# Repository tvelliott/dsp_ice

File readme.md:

<html>

<BR>
<BR><B>DSP_ICE</B>
<BR>
<B>Project Description</B>
<p>DSP_ICE is an ICE40-8K FPGA dev system that has been developed using gcc and
Project Icestorm toolchains.  The hardware has been fully tested except for the
PDM microphone.  Firmware/HDL examples are provided to test the hardware,
including an 8-channel, multi-waveform audio synthesizer and peak amplitude,
frequency measurement via CMSIS DSP FFT functions utilizing the LTC1420 ADC
expansion module.
</p>
<BR>
<B>Why Develop Another ICE40 Dev Board?</B>
<p>
DSP ICE was developed because other boards didn't have all the features desired.
The ultimate goal is to develop an SDR with swappable analog/RF front-ends.
Desired features that drove the development were:
<BR>1) 10/100 Ethernet
<BR>2) 8K ICE 40 device that could be done with 5mil spaced, 4-layer pcb
<BR>3) I2S audio output
<BR>4) STM32F4 device that is foot-print compatible with F7 and H7 series for future
<BR>5) 16-bit FSMC memory-bus interface between the MCU and FPGA
<BR>6) Low-noise power supplies with plenty of current for expansion modules
<BR>7) Plenty of expansion I/O pins designed to utilize upper limits on frequency with ICE40
</p>

<H3><a href="https://raw.githubusercontent.com/tvelliott/dsp_ice/master/firmware/audio_synth_test/dsp_ice_audio_synth_test.mp3">8-channel audio synth test.mp3</a> audio output from example audio-synth implemented in Verilog</H3> 

<BR>
<BR>
<B>Features:</B>
<BR>
<BR>STM32F417 MCU  (upgradable with drop-in for F7 and H7 series up to 400 MHz)
<BR>ICE40HX8K-CT256 FPGA (largest ICE40 device available)
<BR>16-Bit FSMC interface between MCU <-> FPGA.  Interface clock is running @ 80 MHz
<BR>10-100 Mbps Ethernet interface  (firmware includes iperf3 server for testing bandwidth)
<BR>ST-Link programming header  (can use STM32F4-Discovery as a programming device)
<BR>I2S Audio interface  (firmware includes example of 8-channel audio synth with sawtooth, pulse, noise waveforms and a song playback via I2S)
<BR>4 PMOD-Like ports  (include 5V and 3.3V and 8 I/O pins x 4)
<BR>USB FTDI-based serial interface  (update 8/13/2017 firmware to test the uart interface has been added)
<BR>40 MHz TCXO crystal driving both FPGA and MCU  (MCU clock div/2)

<BR>
<BR>
<B>Verilog Source Is Here</B>
<BR>
<a href="https://github.com/tvelliott/dsp_ice/tree/master/firmware/fpga/src">/firmware/fpga/src</a>
<BR>

<BR>
<B>DSP ICE MCU 16-bit Memory-Mapped FPGA registers</B>
<BR>
<pre>
0x60000000   spi1_ctrl
0x60000002   spi1_data_in
0x60000004   spi1_data_out
0x60000006   spi1_cs_ctrl

0x60000008   spi2_ctrl
0x6000000a   spi2_data_in
0x6000000c   spi2_data_out
0x6000000e   spi2_cs_ctrl

0x60000010   adc_data  (LTC1420 hw module, read-only, bit0 is OF) 

0x60001000   audio_ctrl
0x60001002   left_sample
0x60001004   right_sample
0x60001006   tone1_freq
0x60001008   tone2_freq
0x6000100a   tone3_freq
0x6000100c   tone4_freq
0x6000100e   tone5_freq
0x60001010   tone6_freq
0x60001012   tone7_freq
0x60001014   tone8_freq
0x60001016   waveform_ctrl

0x6000f000   16-bit random number (ro)
</pre>

<B>PCB Design</B>
<BR>4 layers
<BR>Designed for OSH Park 4 layer service.  (5 mil spacing)
<BR>Have assembled 4 boards without any connectivity issues on the 256-pin BGA

<B>Left To Do</B>
<BR>The PDM michrophone has not been tested yet due to trouble getting the part.  
<BR>Digikey has the part in stock, but Cirrus Logic will not allow them to sell 
<BR>it to certain individuals including the author of this project. There were
<BR>no further explanations from Cirrus Logic.
<BR>
<BR>
<B>Building The Firmware</B>
<PRE>
Instructions (tested on Debian 8 system)

1) download GNU ARM Embedded Toolchain from here:

<a href="https://launchpad.net/gcc-arm-embedded"> https://launchpad.net/gcc-arm-embedded </a>

The test firmare was compiled with version:
gcc-arm-none-eabi-5_4-2016q3-20160926-linux.tar.bz2

2) *edit the makedefs_fp and change PRE_PREFIX to point to the absolute path of
the toolchain directory *optionally,  move the uncompressed toolchain folder to
the project folder and rename to gnu_arm_toolchain

3) From the project directory, In order to re-build the FPGA binary image, type
'sh build_fpga_image.sh'  (requires that Project Icestorm tools are installed)

  yosys  (synthesis tool)  <a href="http://www.clifford.at/icestorm/"> http://www.clifford.at/icestorm/</a>
  ice-tools  (tools for maniuplating text/binaries and programming dev boards) 
  arache-pnr  (place-and-route)  <a href="https://github.com/cseed/arachne-pnr"> https://github.com/cseed/arachne-pnr </a>

  Note:  The fpga binary configuration image will be compressed and converted
to a header file for inclusion to the MCU firmware image:  fpga_image.h The
compressed image in fpga_image.h will be included in fpga.c on the next mcu
firmware build  (step 4) The MCU uncompresses and transfers the fpga config
image during startup.

4) From the project directory, type 'make clean' followed by  'make' The
resulting binary will be copied to /tmp folder and also the build_image folder
in the current project directory Note: the prototypes in protos can be
re-generated with 'make genprotos' if cfunctions is installed.

5) An ST-Link programmer can be used to load the resulting binary
(main_image_0x8000000.bin) to address 0x8000000

   A $15 STM32F4 Discovery board with the jumpers set to "ST Link"  (pulled
off) and a straight-thru, 6-pin 0.1" pitch cable will work.

   Follow instructions for compiling OpenOCD  <a href="http://openocd.org/"> http://openocd.org/</a>

   start the debugger:  'sudo src/openocd -s tcl -f tcl/board/stm32f4discovery.cfg'

   'telnet localhost 4444'
    > reset halt
    > flash write_image erase build_image/main_image_0x8000000.bin 0x8000000

6) Test the hardware.
   telnet 192.168.1.240   (default ip address.  edit this in config.c)
   
Trying 192.168.1.240...
Connected to 192.168.1.240.
Escape character is '^]'.

Connected To STM32F417 Running @ 168 MHz
DSP_Ice 192.168.1.240:~$ help

Available commands:

testmem
testsnd
testflash1
testflash2
testadc
reset
exit

DSP_Ice 192.168.1.240:~$ testadc
<B>Example measurement of 500 KHz sine wave, 100mVpp utilize LTC1420 ADC HW module</B>
<B>This example utilizes the CMSIS DSP Co-Processor functions of the MCU for FFT calcs.</B>
<B>Using DMA to transfer ADC results from FPGA BRAM would dramatically improve sample rate</B>
peak signal 502675.781 Hz,  0.107 Volts p-p, elapsed time 3.51 ms  
<a href="https://github.com/tvelliott/dsp_ice/blob/master/hw_modules/ltc1420_adc/fft_plot_500khz_100mVpp.gif">[see fft plot 500khz, 100mV p-p]</a> 
<a href="https://github.com/tvelliott/dsp_ice/blob/master/hw_modules/ltc1420_adc/ltc1420_capture_3.5vpp_no_filter_325khz_freqdomain.gif">[see fft plot 325Khz, 3500mV p-p]</a> 
<a href="https://github.com/tvelliott/dsp_ice/blob/master/hw_modules/ltc1420_adc/ltc1420_capture_3.5vpp_no_filter_500khz_timedomain.gif">[see time-domain plot 500khz, 3500mV p-p]</a> 
 
DSP_Ice 192.168.1.240:~$ testmem   (this tests the 16-bit FSMC memmory-mapped, MCU<->FPGA interface)

x100x (FPGA D-REG), 4015677440 bytes r/w random access, current vals: f3e7,f3e7, errors: 0
0x100x (FPGA D-REG), 4015685632 bytes r/w random access, current vals: 69c4,69c4, errors: 0
0x100x (FPGA D-REG), 4015693824 bytes r/w random access, current vals: af9a,af9a, errors: 0
0x100x (FPGA D-REG), 4015702016 bytes r/w random access, current vals: bc6a,bc6a, errors: 0
0x100x (FPGA D-REG), 4015710208 bytes r/w random access, current vals: 8732,8732, errors: 0
0x100x (FPGA D-REG), 4015718400 bytes r/w random access, current vals: 06f4,06f4, errors: 0
0x100x (FPGA D-REG), 4015726592 bytes r/w random access, current vals: 32af,32af, errors: 0
.....

DSP_Ice 192.168.1.240:~$ sh test_iperf.sh

Connecting to host 192.168.1.240, port 5201
[  4] local 192.168.1.3 port 45612 connected to 192.168.1.240 port 5201
[ ID] Interval           Transfer     Bandwidth       Retr  Cwnd
[  4]   0.00-1.00   sec  8.91 MBytes  74.7 Mbits/sec    0   14.3 KBytes       
[  4]   1.00-2.00   sec  8.88 MBytes  74.5 Mbits/sec    0   14.3 KBytes       
[  4]   2.00-3.00   sec  8.86 MBytes  74.3 Mbits/sec    0   14.3 KBytes       
[  4]   3.00-4.00   sec  8.86 MBytes  74.3 Mbits/sec    0   14.3 KBytes       
[  4]   4.00-5.00   sec  8.88 MBytes  74.5 Mbits/sec    0   14.3 KBytes       
[  4]   5.00-6.00   sec  8.87 MBytes  74.4 Mbits/sec    0   14.3 KBytes       
[  4]   6.00-7.00   sec  8.86 MBytes  74.3 Mbits/sec    0   14.3 KBytes       
[  4]   7.00-8.00   sec  8.86 MBytes  74.3 Mbits/sec    0   14.3 KBytes       
[  4]   8.00-9.00   sec  8.86 MBytes  74.3 Mbits/sec    0   14.3 KBytes       

iperf Done.

....
DSP_Ice 192.168.1.240:~$ testsnd   (song playback via 8-channel audio synth implemented on fpga)

change instrument: ch: 0,  instr: 29, mask: 5555
chan: 0, freq: 554
change instrument: ch: 1,  instr: 37, mask: 5555
chan: 1, freq: 92
change instrument: ch: 2,  instr: 16, mask: 5575
chan: 2, freq: 233
change instrument: ch: 3,  instr: 29, mask: 5575
chan: 3, freq: 370
change instrument: ch: 4,  instr: 16, mask: 5775
chan: 4, freq: 131
change instrument: ch: 5,  instr: 16, mask: 5f75
chan: 5, freq: 131
duration: 91
duration: 91
chan: 0, freq: 494
chan: 3, freq: 330
duration: 91
duration: 91
chan: 2, freq: 208
chan: 0, freq: 554
chan: 3, freq: 370
duration: 91
duration: 91
chan: 0, freq: 494
chan: 3, freq: 330
duration: 91
duration: 91
chan: 0, freq: 554
chan: 3, freq: 370
duration: 91
duration: 91

<B>Images Of LTC1420 HW Module and PCB cad rendering</B>

....
</PRE>

<B>Links To Similar Projects</B>
<BR>
<a href="https://github.com/emeb/iceRadio">https://github.com/emeb/iceRadio</a>
<BR><BR>
<B>Links To Related Resources</B>
<BR>
<BR><a href="https://launchpad.net/gcc-arm-embedded"> https://launchpad.net/gcc-arm-embedded </a>
<BR><a href="http://www.clifford.at/icestorm/"> http://www.clifford.at/icestorm/</a>
<BR><a href="https://github.com/cseed/arachne-pnr"> https://github.com/cseed/arachne-pnr </a>
<BR><a href="http://openocd.org/"> http://openocd.org/</a>

</html>

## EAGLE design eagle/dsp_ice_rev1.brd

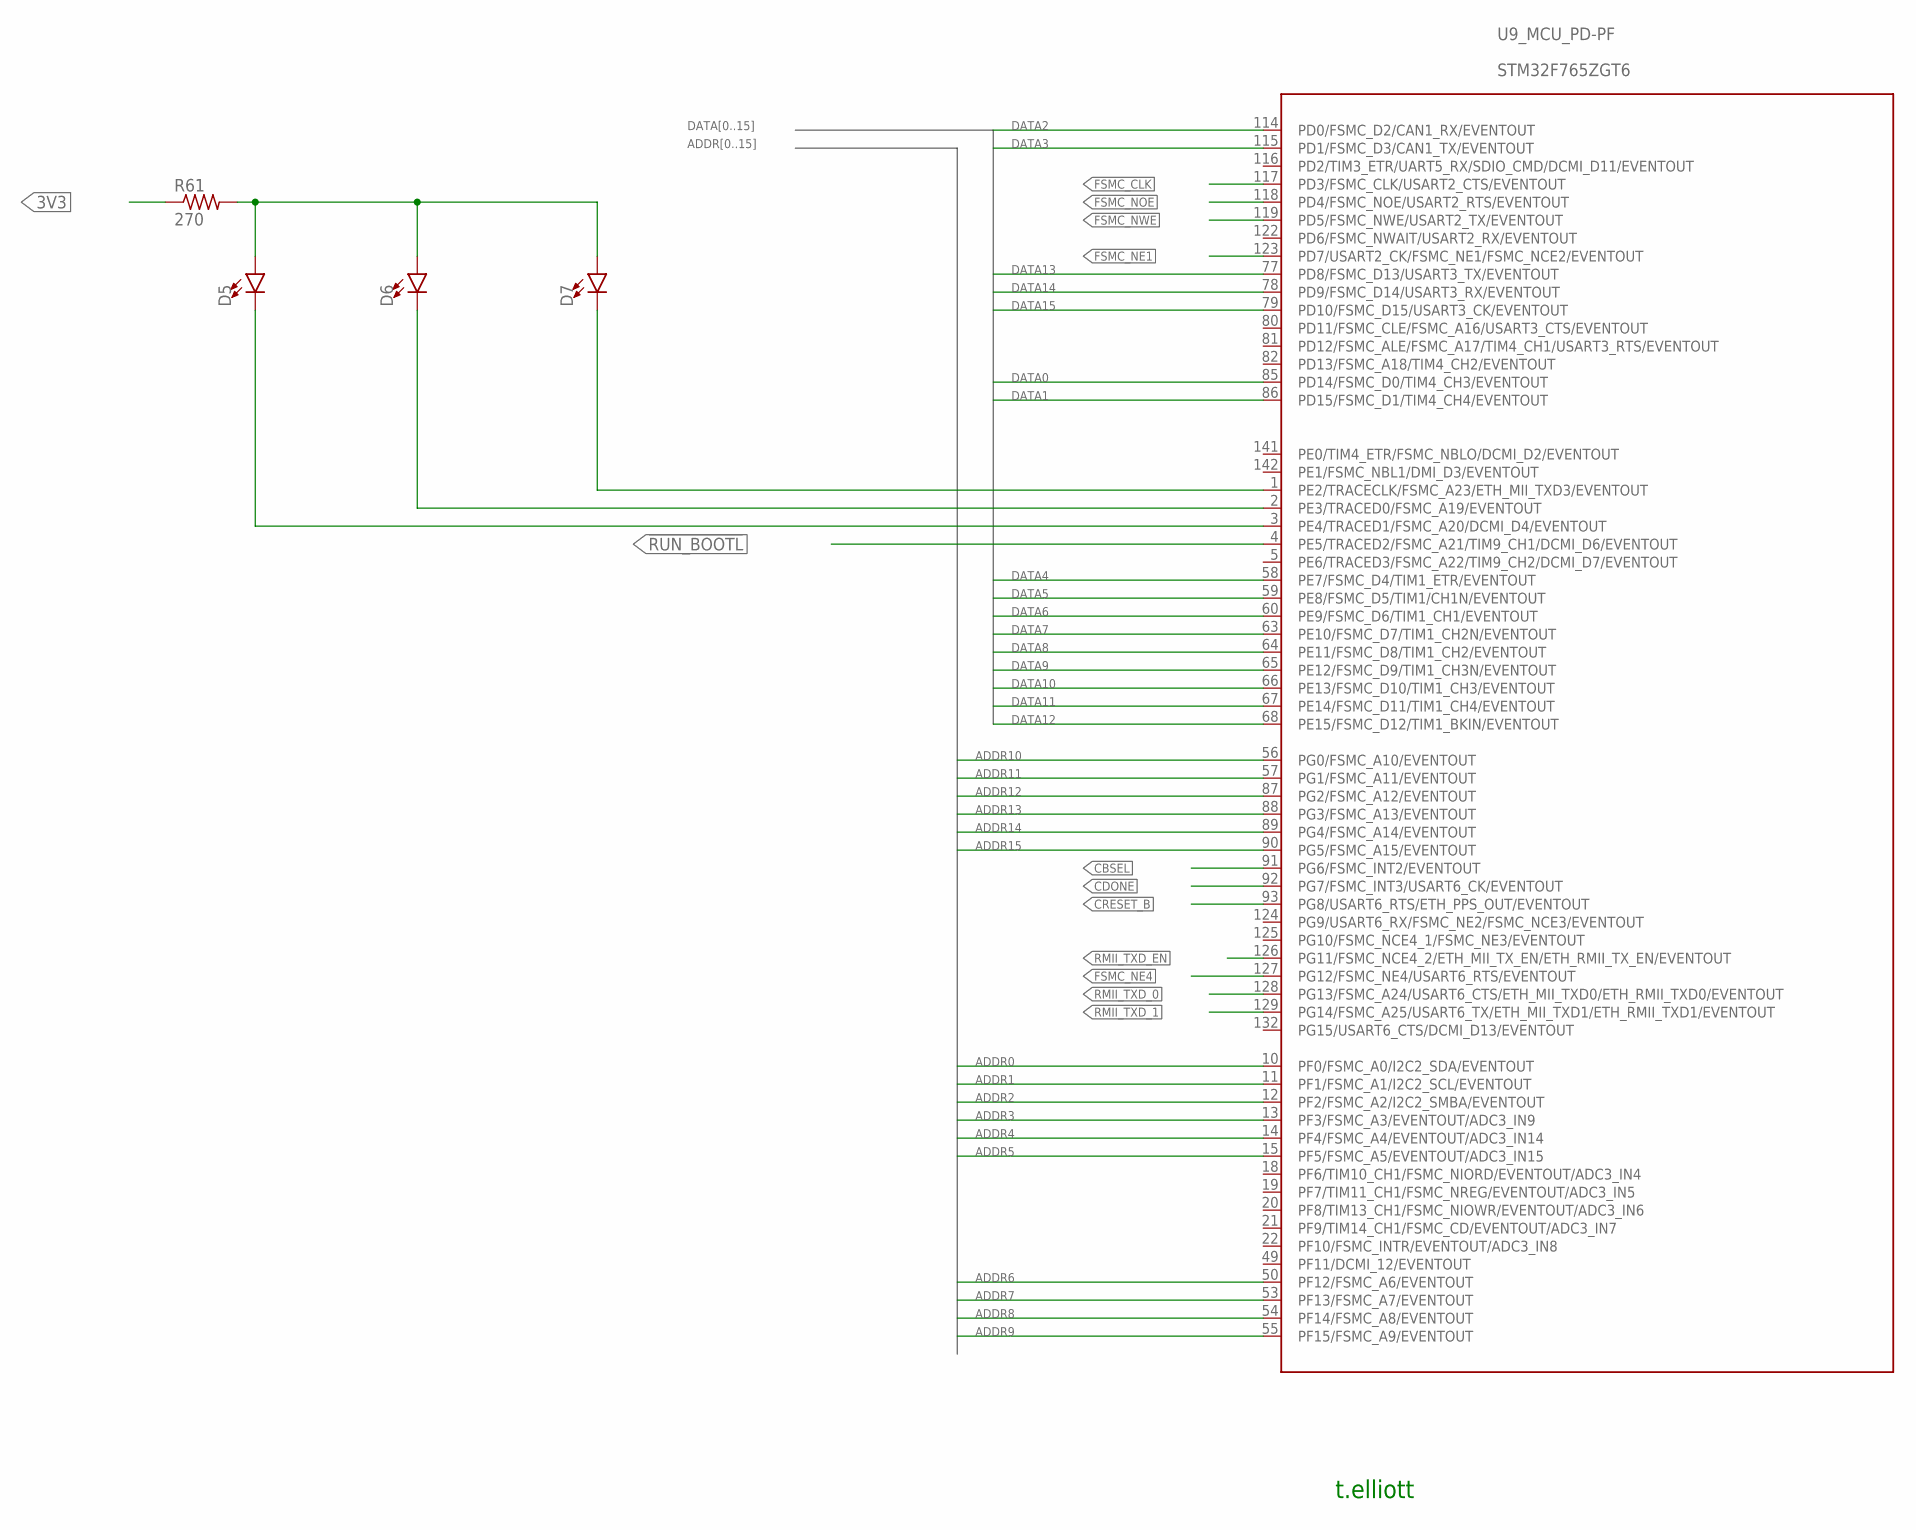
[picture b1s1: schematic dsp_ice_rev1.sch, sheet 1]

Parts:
D5, D6, D7: LED1206; LED-1206
R61: 270; R0603
U9: STM32F765ZGT6; STM32F407_144

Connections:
3V3: R61.1; also elsewhere on the board
!RUN_BOOTL: U9.4 (PE5/TRACED2/FSMC_A21/TIM9_CH1/DCMI_D6/E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); also elsewhere on the board
ADDR0: U9.10 (PF0/FSMC_A0/I2C2_SDA/EVENTOUT); also elsewhere on the board
ADDR1: U9.11 (PF1/FSMC_A1/I2C2_SCL/EVENTOUT); also elsewhere on the board
ADDR2: U9.12 (PF2/FSMC_A2/I2C2_SMBA/EVENTOUT); also elsewhere on the board
ADDR3: U9.13 (PF3/FSMC_A3/EVENTOUT/ADC3_IN9); also elsewhere on the board
ADDR4: U9.14 (PF4/FSMC_A4/EVENTOUT/ADC3_IN14); also elsewhere on the board
ADDR5: U9.15 (PF5/FSMC_A5/EVENTOUT/ADC3_IN15); also elsewhere on the board
ADDR6: U9.50 (PF12/FSMC_A6/EVENTOUT); also elsewhere on the board
ADDR7: U9.53 (PF13/FSMC_A7/EVENTOUT); also elsewhere on the board
ADDR8: U9.54 (PF14/FSMC_A8/EVENTOUT); also elsewhere on the board
ADDR9: U9.55 (PF15/FSMC_A9/EVENTOUT); also elsewhere on the board
ADDR10: U9.56 (PG0/FSMC_A10/EVENTOUT); also elsewhere on the board
ADDR11: U9.57 (PG1/FSMC_A11/EVENTOUT); also elsewhere on the board
ADDR12: U9.87 (PG2/FSMC_A12/EVENTOUT); also elsewhere on the board
ADDR13: U9.88 (PG3/FSMC_A13/EVENTOUT); also elsewhere on the board
ADDR14: U9.89 (PG4/FSMC_A14/EVENTOUT); also elsewhere on the board
ADDR15: U9.90 (PG5/FSMC_A15/EVENTOUT); also elsewhere on the board
CBSEL: U9.91 (PG6/FSMC_INT2/EVENTOUT); also elsewhere on the board
CDONE: U9.92 (PG7/FSMC_INT3/USART6_CK/EVENTOUT); also elsewhere on the board
CRESET_B: U9.93 (PG8/USART6_RTS/ETH_PPS_OUT/EVENTOUT); also elsewhere on the board
DATA0: U9.85 (PD14/FSMC_D0/TIM4_CH3/EVENTOUT); also elsewhere on the board
DATA1: U9.86 (PD15/FSMC_D1/TIM4_CH4/EVENTOUT); also elsewhere on the board
DATA2: U9.114 (PD0/FSMC_D2/CAN1_RX/EVENTOUT); also elsewhere on the board
DATA3: U9.115 (PD1/FSMC_D3/CAN1_TX/EVENTOUT); also elsewhere on the board
DATA4: U9.58 (PE7/FSMC_D4/TIM1_ETR/EVENTOUT); also elsewhere on the board
DATA5: U9.59 (PE8/FSMC_D5/TIM1/CH1N/EVENTOUT); also elsewhere on the board
DATA6: U9.60 (PE9/FSMC_D6/TIM1_CH1/EVENTOUT); also elsewhere on the board
DATA7: U9.63 (PE10/FSMC_D7/TIM1_CH2N/EVENTOUT); also elsewhere on the board
DATA8: U9.64 (PE11/FSMC_D8/TIM1_CH2/EVENTOUT); also elsewhere on the board
DATA9: U9.65 (PE12/FSMC_D9/TIM1_CH3N/EVENTOUT); also elsewhere on the board
DATA10: U9.66 (PE13/FSMC_D10/TIM1_CH3/EVENTOUT); also elsewhere on the board
DATA11: U9.67 (PE14/FSMC_D11/TIM1_CH4/EVENTOUT); also elsewhere on the board
DATA12: U9.68 (PE15/FSMC_D12/TIM1_BKIN/EVENTOUT); also elsewhere on the board
DATA13: U9.77 (PD8/FSMC_D13/USART3_TX/EVENTOUT); also elsewhere on the board
DATA14: U9.78 (PD9/FSMC_D14/USART3_RX/EVENTOUT); also elsewhere on the board
DATA15: U9.79 (PD10/FSMC_D15/USART3_CK/EVENTOUT); also elsewhere on the board
FSMC_CLK: U9.117 (PD3/FSMC_CLK/USART2_CTS/EVENTOUT); also elsewhere on the board
FSMC_NE1: U9.123 (PD7/USART2_CK/FSMC_NE1/FSMC_NCE2/EVENTO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); also elsewhere on the board
FSMC_NE4: U9.127 (PG12/FSMC_NE4/USART6_RTS/EVENTOUT); also elsewhere on the board
FSMC_NOE: U9.118 (PD4/FSMC_NOE/USART2_RTS/EVENTOUT); also elsewhere on the board
FSMC_NWE: U9.119 (PD5/FSMC_NWE/USART2_TX/EVENTOUT); also elsewhere on the board
unnamed: D5.A, D6.A, D7.A, R61.2
unnamed: D7.C, U9.1 (PE2/TRACECLK/FSMC_A23/ETH_MII_TXD3/EVEN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)
unnamed: D6.C, U9.2 (PE3/TRACED0/FSMC_A19/EVENTOUT)
unnamed: D5.C, U9.3 (PE4/TRACED1/FSMC_A20/DCMI_D4/EVENTOUT)
RMII_TXD_0: U9.128 (PG13/FSMC_A24/USART6_CTS/ETH_MII_TXD0/E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); also elsewhere on the board
RMII_TXD_1: U9.129 (PG14/FSMC_A25/USART6_TX/ETH_MII_TXD1/ET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); also elsewhere on the board
RMII_TXD_EN: U9.126 (PG11/FSMC_NCE4_2/ETH_MII_TX_EN/ETH_RMII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); also elsewhere on the board

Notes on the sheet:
t.elliott

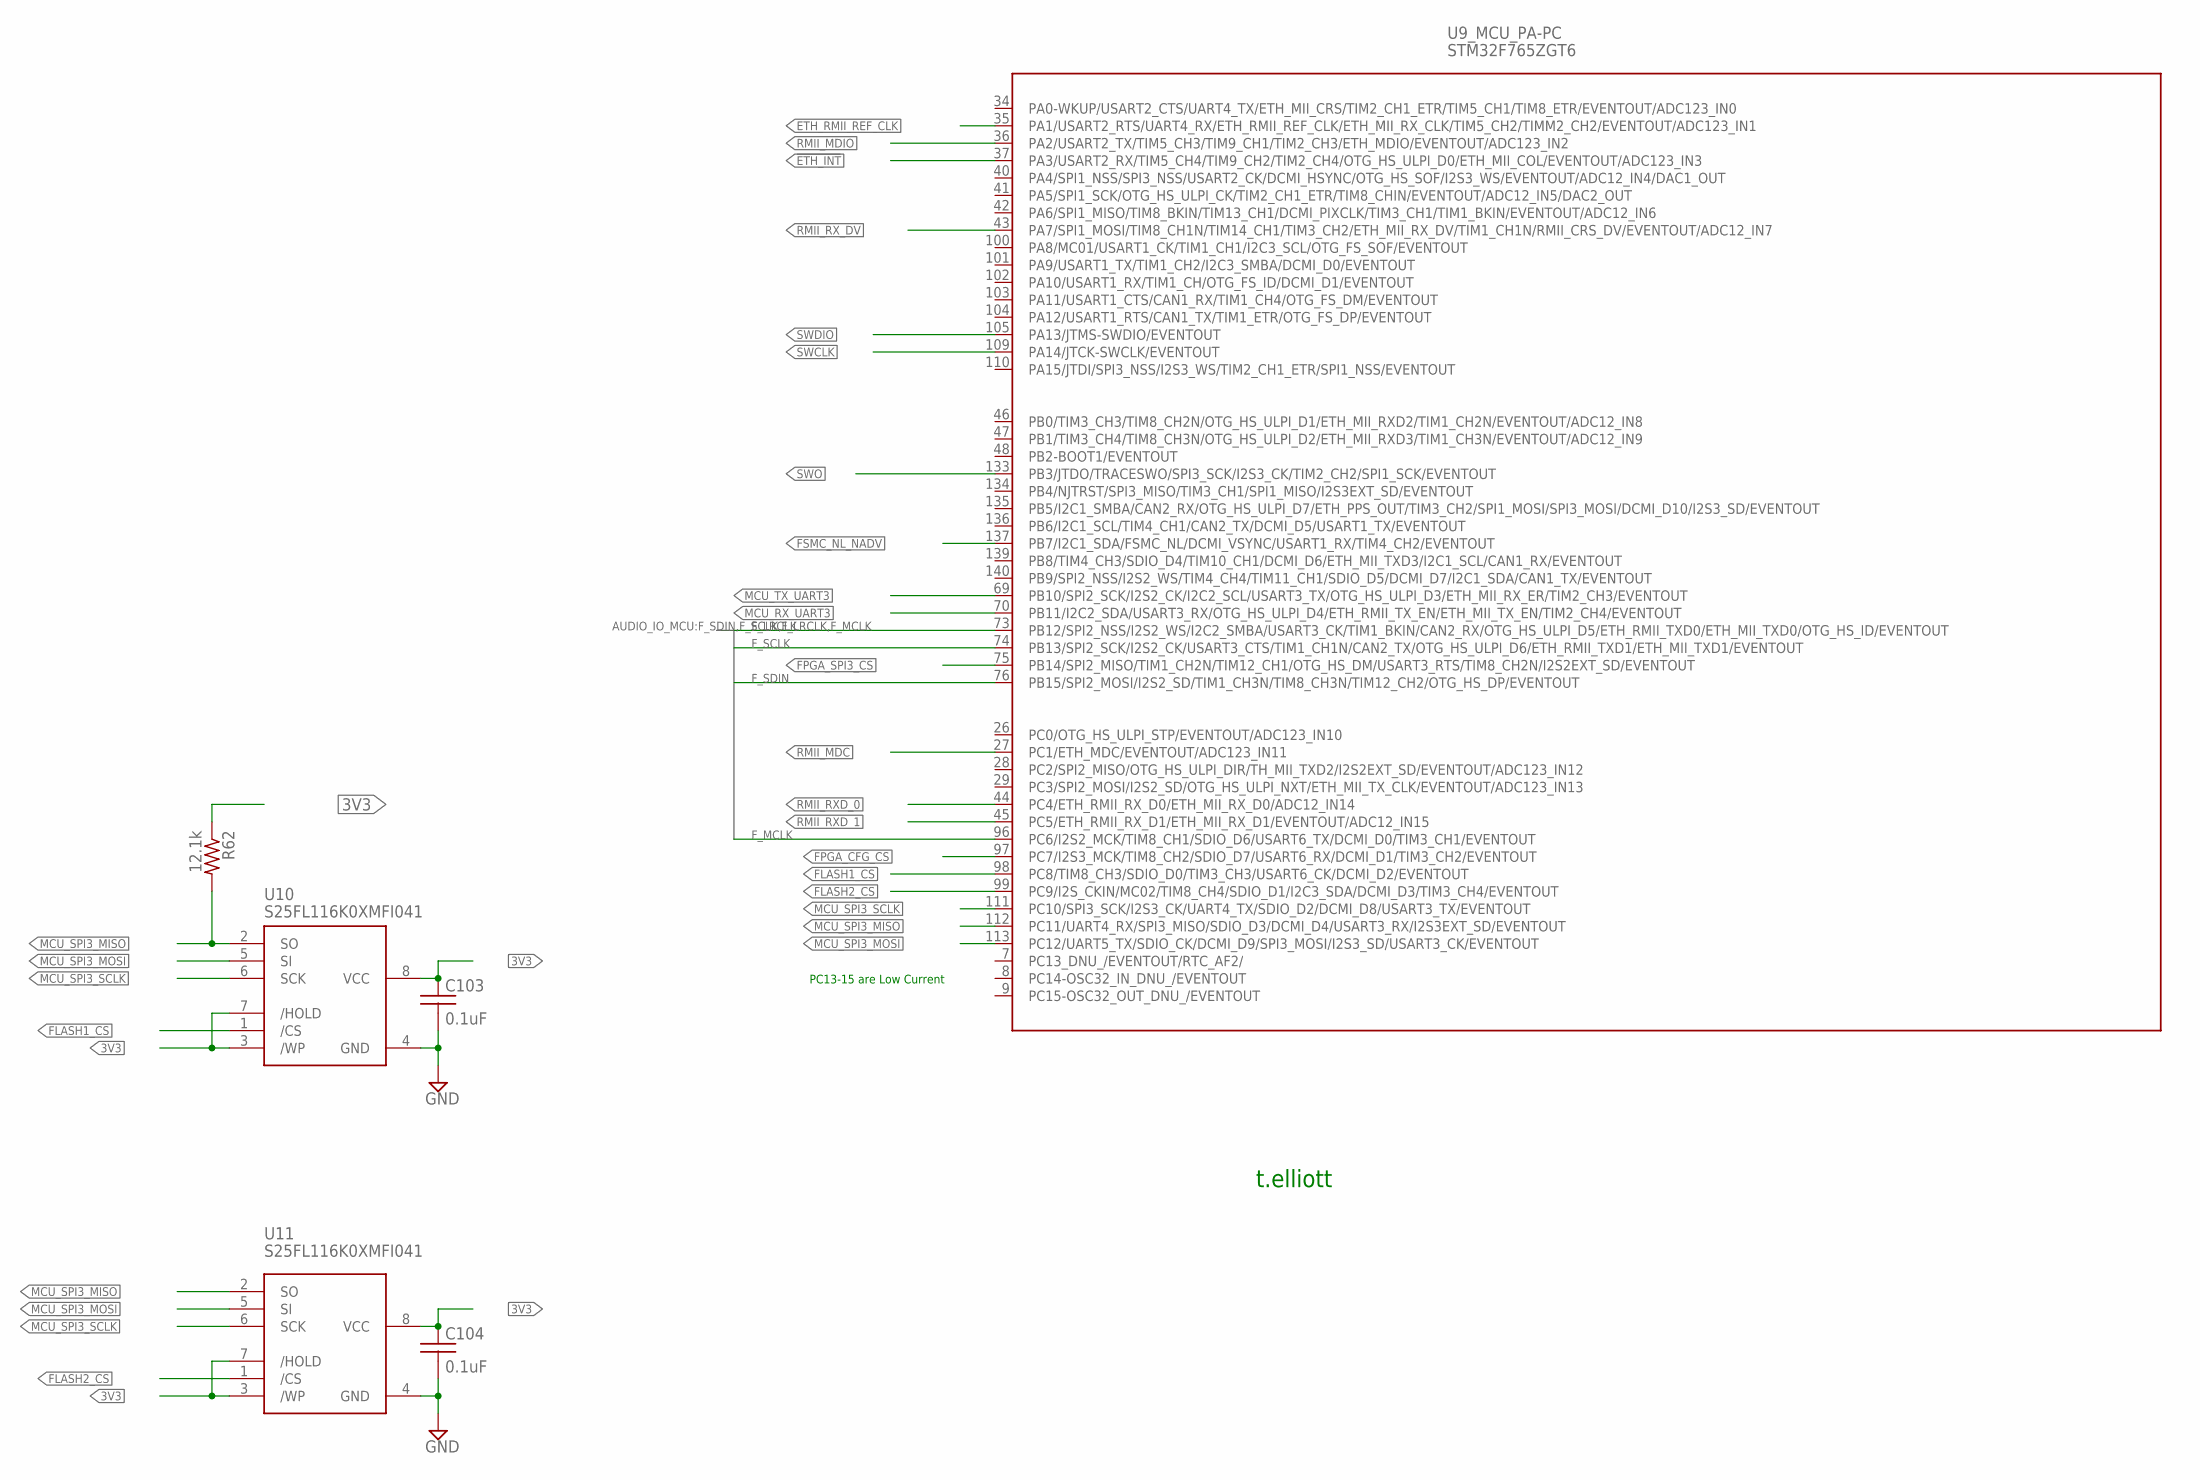
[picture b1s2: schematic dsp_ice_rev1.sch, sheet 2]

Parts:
C103, C104: 0.1uF; C0603
R62: 12.1k; R0603
U9: STM32F765ZGT6; STM32F407_144
U10, U11: S25FL116K0XMFI041; SO8

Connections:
3V3: C103.1, C104.1, R62.1, U10.3 (/WP), U10.7 (/HOLD), U10.8 (VCC), U11.3 (/WP), U11.7 (/HOLD), U11.8 (VCC); also elsewhere on the board
!ETH_INT: U9.37 (PA3/USART2_RX/TIM5_CH4/TIM9_CH2/TIM2_CH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); also elsewhere on the board
ETH_RMII_REF_CLK: U9.35 (PA1/USART2_RTS/UART4_RX/ETH_RMII_REF_CL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); also elsewhere on the board
FLASH1_CS: U9.98 (PC8/TIM8_CH3/SDIO_D0/TIM3_CH3/USART6_CK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), U10.1 (/CS)
FLASH2_CS: U9.99 (PC9/I2S_CKIN/MC02/TIM8_CH4/SDIO_D1/I2C3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), U11.1 (/CS)
FPGA_CFG_CS: U9.97 (PC7/I2S3_MCK/TIM8_CH2/SDIO_D7/USART6_RX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); also elsewhere on the board
FPGA_SPI3_CS: U9.75 (PB14/SPI2_MISO/TIM1_CH2N/TIM12_CH1/OTG_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); also elsewhere on the board
FSMC_NL_NADV: U9.137 (PB7/I2C1_SDA/FSMC_NL/DCMI_VSYNC/USART1_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); also elsewhere on the board
F_LRCLK: U9.73 (PB12/SPI2_NSS/I2S2_WS/I2C2_SMBA/USART3_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); also elsewhere on the board
F_MCLK: U9.96 (PC6/I2S2_MCK/TIM8_CH1/SDIO_D6/USART6_TX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); also elsewhere on the board
F_SCLK: U9.74 (PB13/SPI2_SCK/I2S2_CK/USART3_CTS/TIM1_C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); also elsewhere on the board
F_SDIN: U9.76 (PB15/SPI2_MOSI/I2S2_SD/TIM1_CH3N/TIM8_C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); also elsewhere on the board
GND: C103.2, C104.2, U10.4 (GND), U11.4 (GND); also elsewhere on the board
MCU_RX_UART3: U9.70 (PB11/I2C2_SDA/USART3_RX/OTG_HS_ULPI_D4/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); also elsewhere on the board
MCU_SPI3_MISO: R62.2, U9.112 (PC11/UART4_RX/SPI3_MISO/SDIO_D3/DCMI_D4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), U10.2 (SO), U11.2 (SO); also elsewhere on the board
MCU_SPI3_MOSI: U9.113 (PC12/UART5_TX/SDIO_CK/DCMI_D9/SPI3_MOSI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), U10.5 (SI), U11.5 (SI); also elsewhere on the board
MCU_SPI3_SCLK: U9.111 (PC10/SPI3_SCK/I2S3_CK/UART4_TX/SDIO_D2/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), U10.6 (SCK), U11.6 (SCK); also elsewhere on the board
MCU_TX_UART3: U9.69 (PB10/SPI2_SCK/I2S2_CK/I2C2_SCL/USART3_T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); also elsewhere on the board
RMII_MDC: U9.27 (PC1/ETH_MDC/EVENTOUT/ADC123_IN11); also elsewhere on the board
RMII_MDIO: U9.36 (PA2/USART2_TX/TIM5_CH3/TIM9_CH1/TIM2_CH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); also elsewhere on the board
RMII_RXD_0: U9.44 (PC4/ETH_RMII_RX_D0/ETH_MII_RX_D0/ADC12_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); also elsewhere on the board
RMII_RXD_1: U9.45 (PC5/ETH_RMII_RX_D1/ETH_MII_RX_D1/EVENTO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); also elsewhere on the board
RMII_RX_DV: U9.43 (PA7/SPI1_MOSI/TIM8_CH1N/TIM14_CH1/TIM3_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); also elsewhere on the board
SWCLK: U9.109 (PA14/JTCK-SWCLK/EVENTOUT); also elsewhere on the board
SWDIO: U9.105 (PA13/JTMS-SWDIO/EVENTOUT); also elsewhere on the board
SWO: U9.133 (PB3/JTDO/TRACESWO/SPI3_SCK/I2S3_CK/TIM2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); also elsewhere on the board

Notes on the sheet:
PC13-15 are Low Current
t.elliott

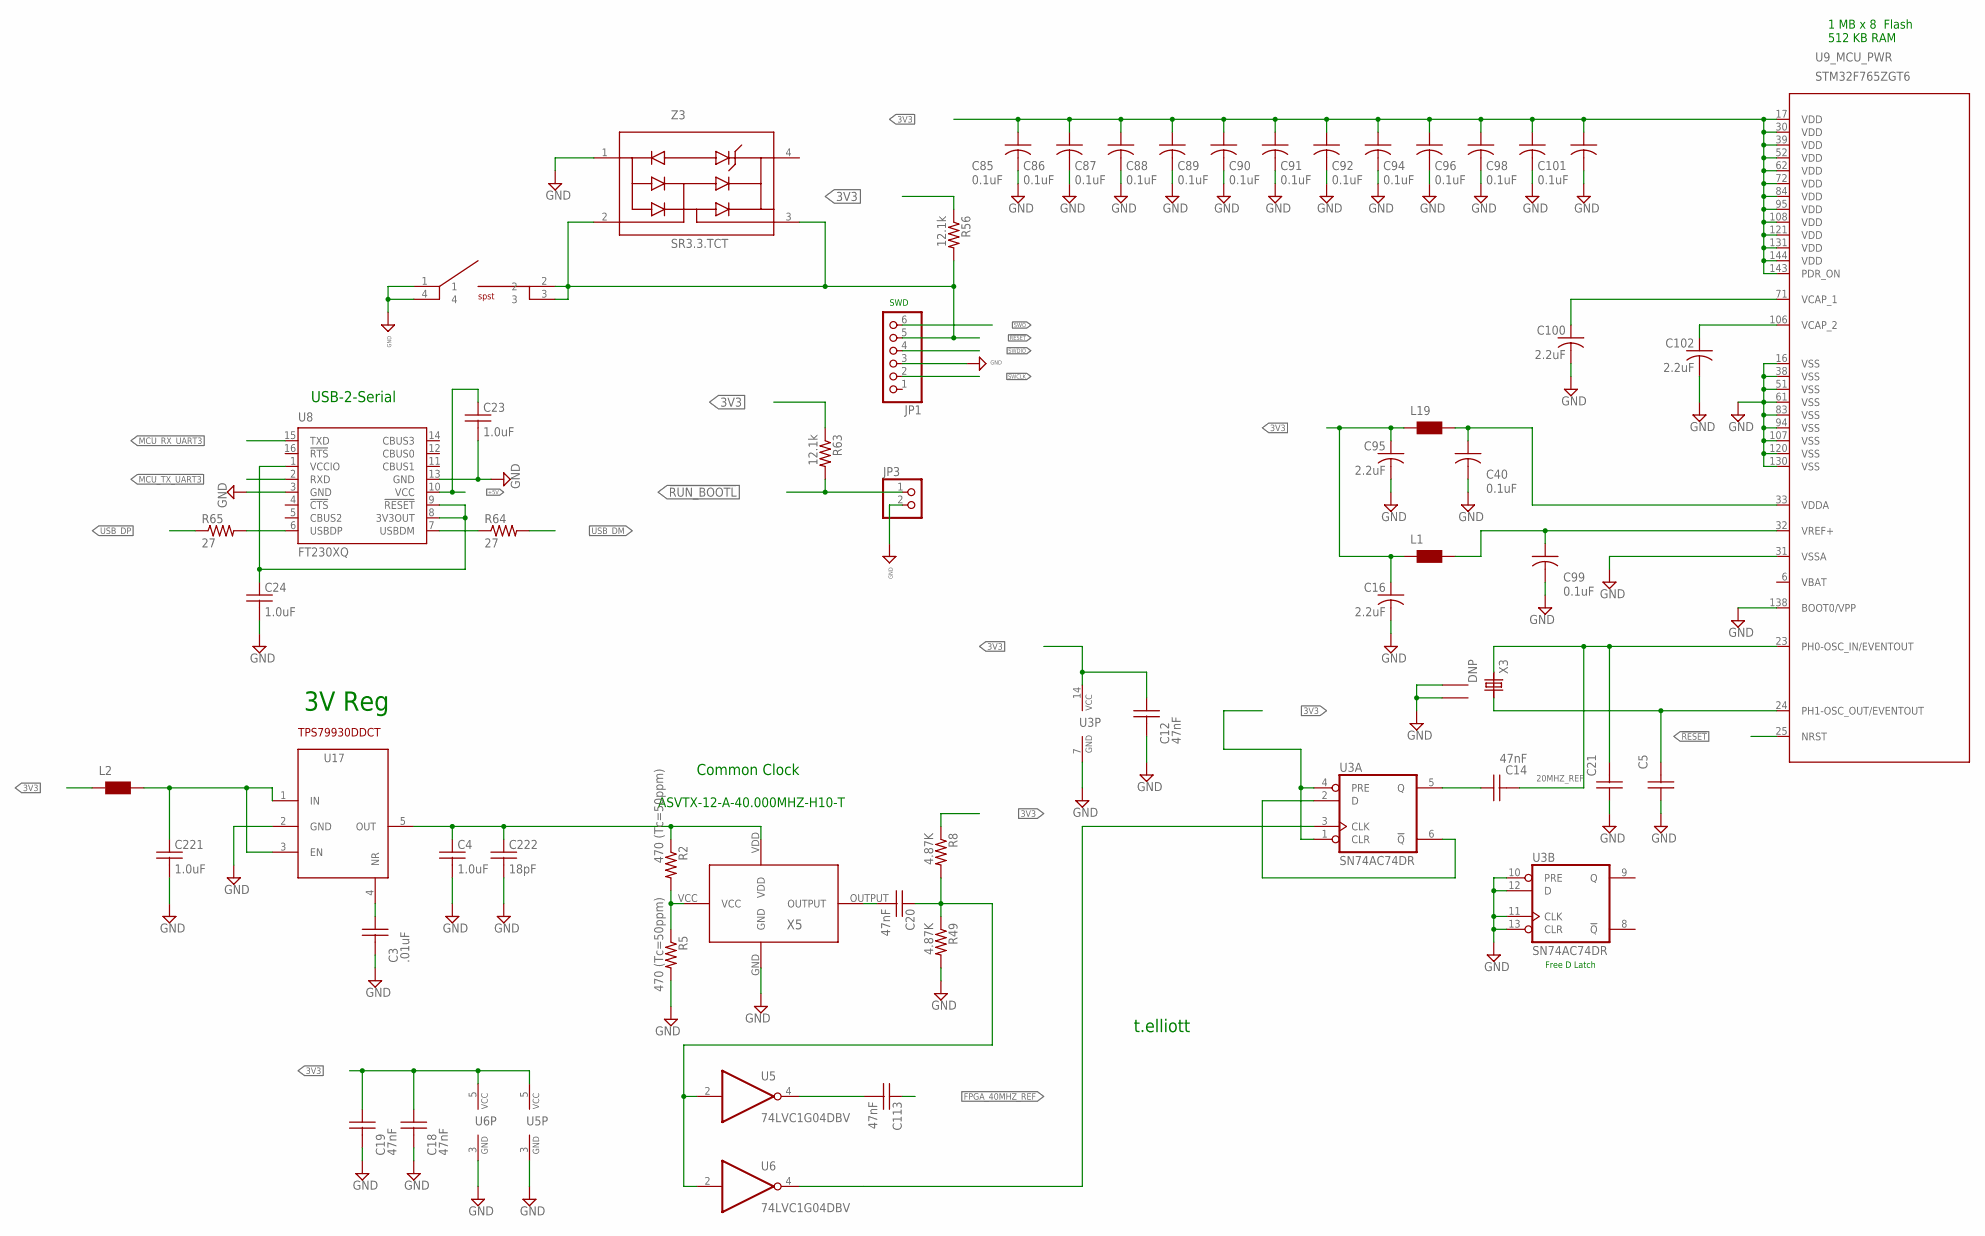
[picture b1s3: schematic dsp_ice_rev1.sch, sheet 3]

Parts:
C3: .01uF; C0402
C4, C23, C24, C221: 1.0uF; C0402
C5, C21: C-USC0402; C0402
C12, C14, C18, C19, C20, C113: 47nF; C0402
C16, C95, C100, C102: 2.2uF; C0805
C40, C85, C86, C87, C88, C89, C90, C91, C92, C94, C96, C98, C99, C101: 0.1uF; 0402
C222: 18pF; C0402
JP1: PINHD-1X6; 1X06
JP3: PINHD-1X2; 1X02
L1, L19: WE-CBF_0603; 0603
L2: WE-CBF_0402; 0402
R2, R5: 470 (Tc=50ppm); R0402
R8, R49: 4.87K; R0603
R56, R63: 12.1k; R0603
R64, R65: 27; R0603
SW3: HOKURIKU_KSM06_6X6MM_SWITCH1; TACTILE_6X6MM
U3: SN74AC74DR; SO14
U5, U6: 74LVC1G04DBV; SOT23-5
U8: FT230XQ; QFN16
U9: STM32F765ZGT6; STM32F407_144
U17: TPS799X; SOT23-6
X3: DNP; ECS-250-20-30B-DU_CRYSTAL
X5: ASVTX-12-A-40.000MHZ-H10-T; CRYSTAL_2.5_2MM
Z3: SR3.3.TCT; SR2.8.TCT_1PRIMARY

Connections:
3V: C4.1, C222.1, R2.1, U17.5 (OUT), X5.VDD
3V3: C12.1, C16.1, C18.1, C19.1, C85.1 (A), C86.1 (A), C87.1 (A), C88.1 (A), C89.1 (A), C90.1 (A), C91.1 (A), C92.1 (A), C94.1 (A), C95.1, C96.1 (A), C98.1 (A), C101.1 (A), L1.1, L2.1, L19.1, R8.1, R56.1, R63.1, U3.1 (CLR), U3.4 (PRE), U3.14 (VCC), U5.5 (VCC), U6.5 (VCC), U9.17 (VDD), U9.30 (VDD), U9.39 (VDD), U9.52 (VDD), U9.62 (VDD), U9.72 (VDD), U9.84 (VDD), U9.95 (VDD), U9.108 (VDD), U9.121 (VDD), U9.131 (VDD), U9.143 (PDR_ON), U9.144 (VDD); also elsewhere on the board
3V_ANALOG: C99.1 (A), L1.2, U9.32 (VREF+)
20MHZ_REF: C14.2, C21.2, U9.23 (PH0-OSC_IN/EVENTOUT), X3.1
!RESET: JP1.5, R56.2, SW3.2, SW3.3, U9.25 (NRST), Z3.2 (I/O), Z3.3 (I/O); also elsewhere on the board
!RUN_BOOTL: JP3.1, R63.2; also elsewhere on the board
+5V: C23.1, U8.10 (VCC); also elsewhere on the board
FPGA_40MHZ_REF: C113.1; also elsewhere on the board
GND: C3.2, C4.2, C5.1, C12.2, C16.2, C18.2, C19.2, C21.1, C23.2, C24.2, C40.2 (C), C85.2 (C), C86.2 (C), C87.2 (C), C88.2 (C), C89.2 (C), C90.2 (C), C91.2 (C), C92.2 (C), C94.2 (C), C95.2, C96.2 (C), C98.2 (C), C99.2 (C), C100.2, C101.2 (C), C102.2, C221.2, C222.2, JP1.3, JP3.2, R5.2, R49.2, SW3.1, SW3.4, U3.7 (GND), U3.10 (PRE), U3.11 (CLK), U3.12 (D), U3.13 (CLR), U5.3 (GND), U6.3 (GND), U8.3 (GND), U8.13 (GND), U9.16 (VSS), U9.31 (VSSA), U9.38 (VSS), U9.51 (VSS), U9.61 (VSS), U9.83 (VSS), U9.94 (VSS), U9.107 (VSS), U9.120 (VSS), U9.130 (VSS), U9.138 (BOOT0/VPP), U17.2 (GND), X3.GND@1 (1), X3.GND@2 (2), X5.GND, Z3.1 (GND); also elsewhere on the board
MCU_RX_UART3: U8.15 (TXD); also elsewhere on the board
MCU_TX_UART3: U8.2 (RXD); also elsewhere on the board
unnamed: R2.2, R5.1, X5.VCC
unnamed: C221.1, L2.2, U17.1 (IN), U17.3 (EN)
unnamed: U3.2 (D), U3.6 (!Q)
unnamed: C20.2, X5.OUTPUT
unnamed: C113.2, U5.4 (O)
unnamed: U3.3 (CLK), U6.4 (O)
unnamed: C20.1, R8.2, R49.1, U5.2 (I), U6.2 (I)
unnamed: C102.1, U9.106 (VCAP_2)
unnamed: C24.1, U8.1 (VCCIO), U8.8 (3V3OUT), U8.9 (!RESET)
unnamed: C100.1, U9.71 (VCAP_1)
unnamed: C5.2, U9.24 (PH1-OSC_OUT/EVENTOUT), X3.3
unnamed: R64.1, U8.7 (USBDM)
unnamed: R65.2, U8.6 (USBDP)
unnamed: C3.1, U17.4 (NR)
unnamed: C40.1 (A), L19.2, U9.33 (VDDA)
unnamed: C14.1, U3.5 (Q)
SWCLK: JP1.2; also elsewhere on the board
SWDIO: JP1.4; also elsewhere on the board
SWO: JP1.6; also elsewhere on the board
USB_DM: R64.2; also elsewhere on the board
USB_DP: R65.1; also elsewhere on the board

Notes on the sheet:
t.elliott
1 MB x 8 Flash 512 KB RAM
ASVTX-12-A-40.000MHZ-H10-T
3V Reg
SWD
Free D Latch
Common Clock
USB-2-Serial

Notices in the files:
firmware/stm32f4x7_eth_bsp.c:
© COPYRIGHT 2016 STMicroelectronics
Licensed under MCD-ST Liberty SW License Agreement V2, (the "License");
firmware/system_stm32f4xx.c:
© COPYRIGHT 2011 STMicroelectronics
(C) COPYRIGHT 2011 STMicroelectronics *****END OF FILE
parts and their libraries:
cirrus-3: Copyright (C) 2005 by Bob Starr, rtzaudio@mindspring.com
SparkFun-LED: Licensing: Creative Commons ShareAlike 4.0 International - https://creativecommons.org/licenses/by-sa/4.0
